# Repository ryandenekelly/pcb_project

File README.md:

# STM32 PCB Project
**Very much a work in progress**

PCB prototype project using KiCad and based on ST32F411RET7. 
The goal is to utilise the SSD1306 or ST7735 LCD displays and RFM69 radio to make a sensor sever / controller.

## Schematic
### MCU

Circuitry to power microcontroller and its nesessary parts.

### Power

USB-C/Battery power and regulator.

### UART
USB-B UART input.

### Radio and Display
Headers for RFM69 radio and LCD displays

### Input
Push button and encoder input with filtering.

## PCB

First version of PCB

### Top Layer

Top layer containing the signals and power.

### Bottom Layer

Bottom layer containing mostly the GND plane, with some signals from vias.

### Future Improvement

Currently in the proccess of assembling pcb. The wrong size capacitors were ordered for C13 and C14, but were assembled with some reworking.
May need re-design on crystal oscilator to use a part that is more easily hand soldered. Boot and reset nets may need reworking.

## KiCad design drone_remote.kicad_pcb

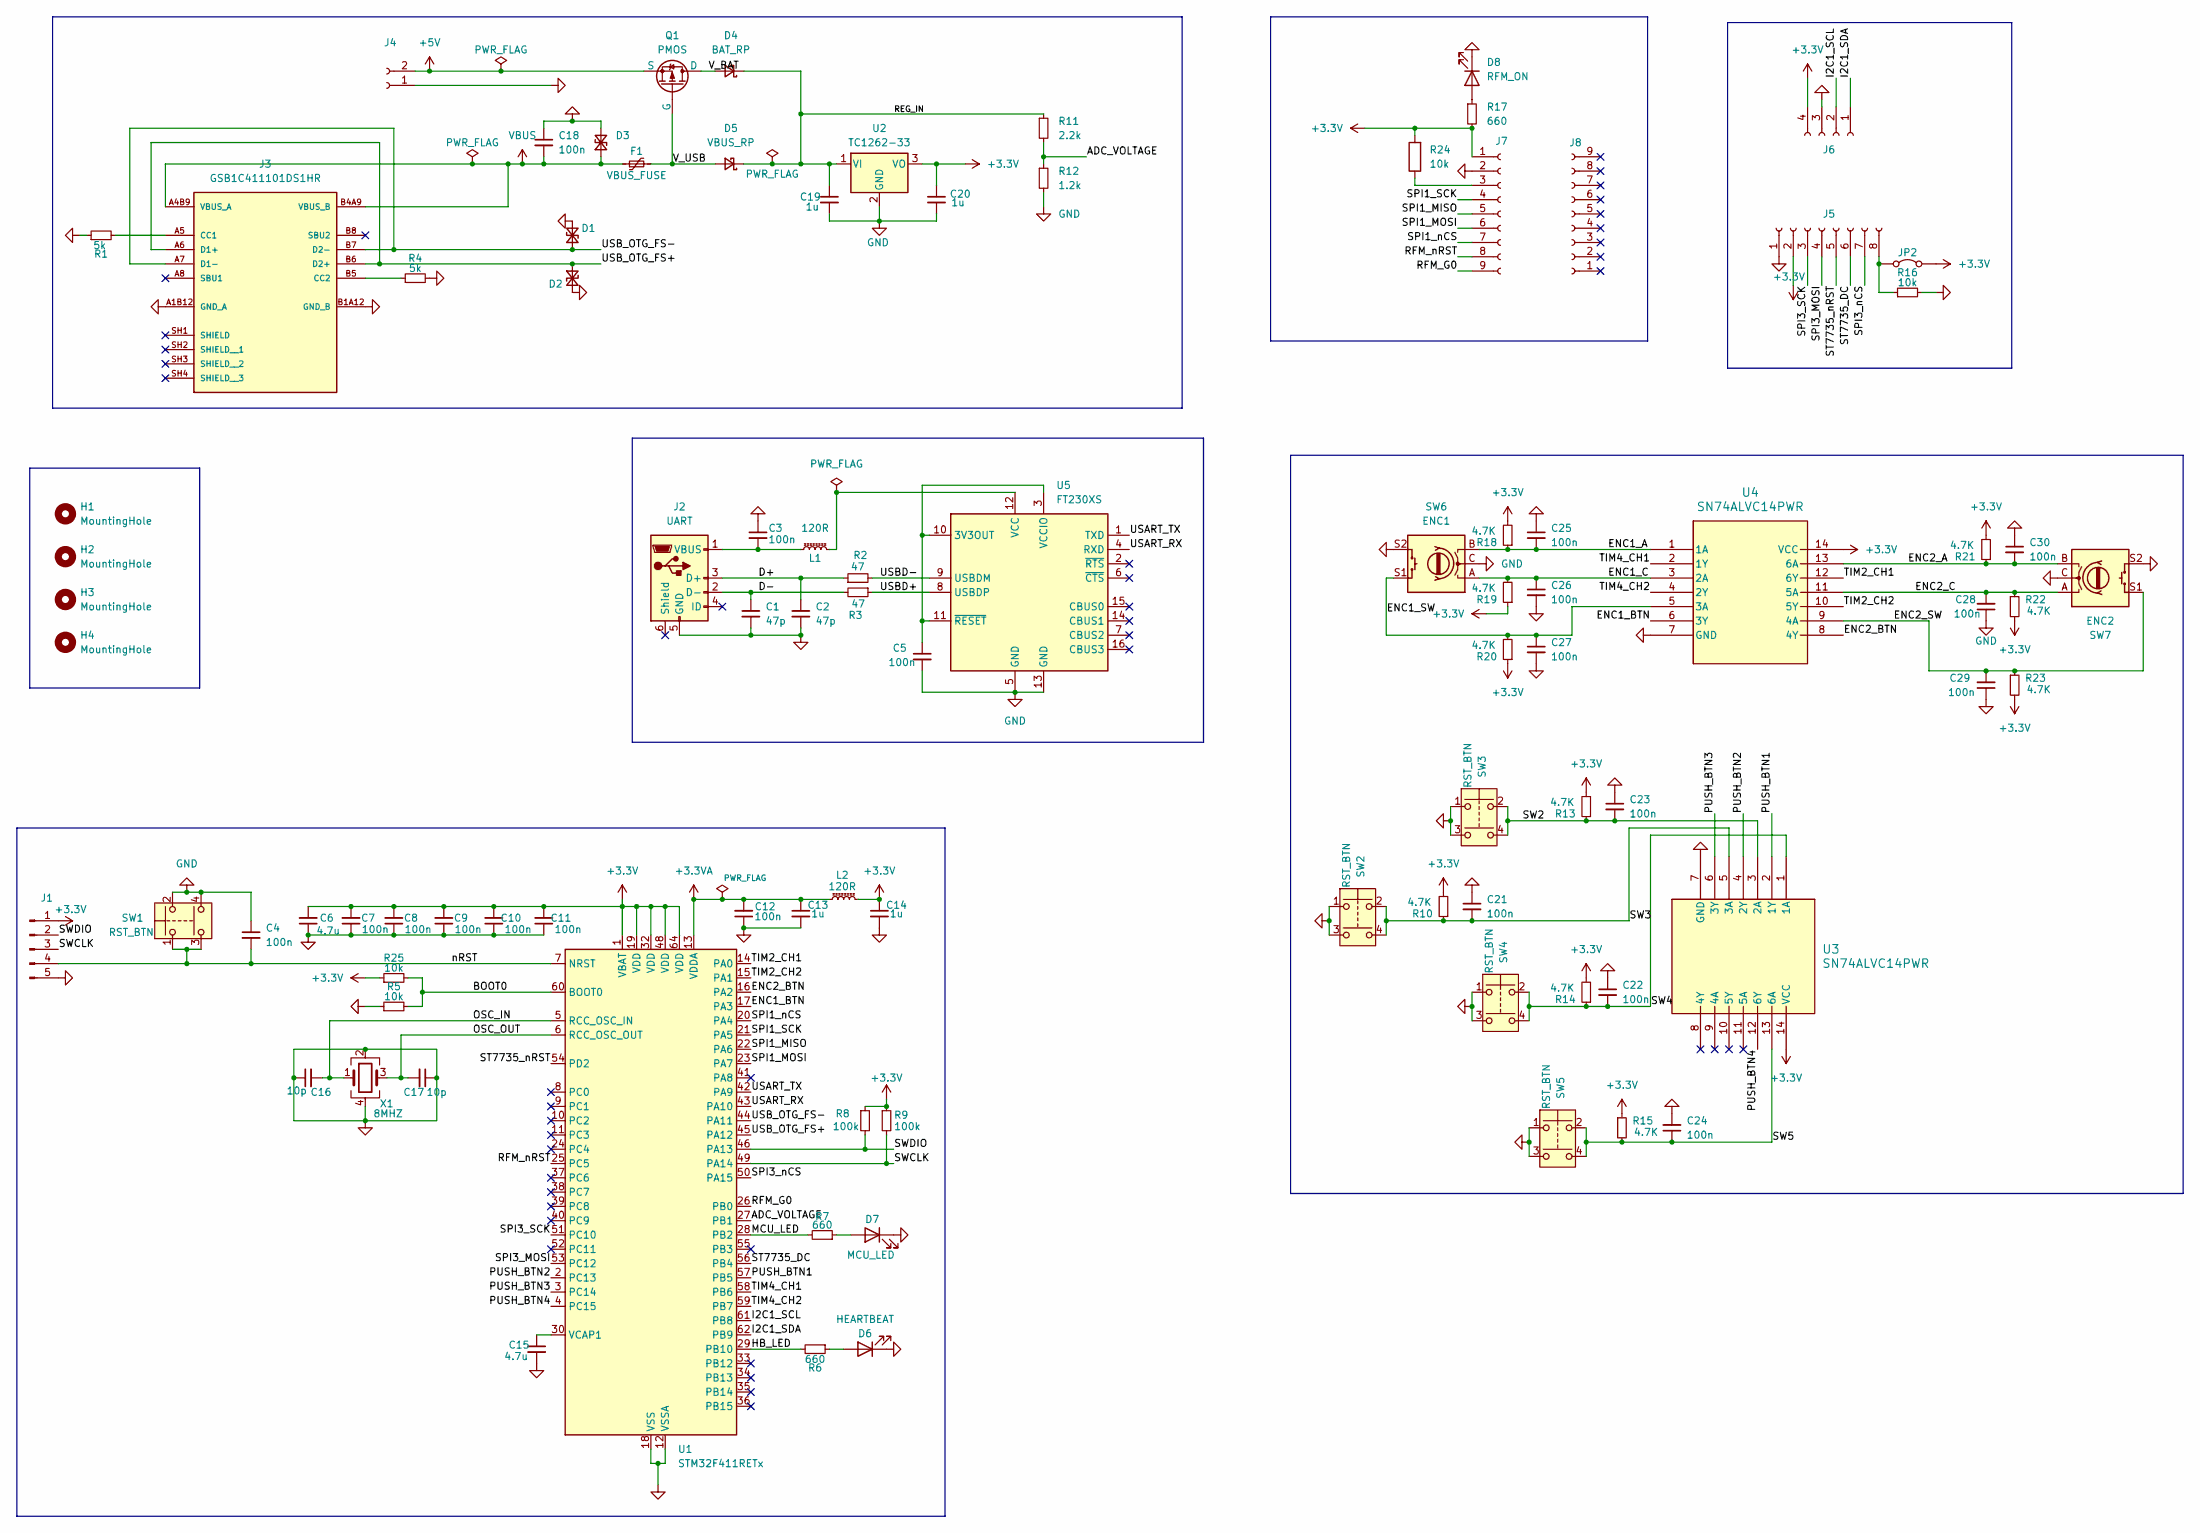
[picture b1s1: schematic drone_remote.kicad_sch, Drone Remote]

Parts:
C1, C2: 47p; C_0402_1005Metric
C3, C4, C5, C18, C21, C22, C23, C24, C25, C26, C27, C28, C29, C30: 100n; C_0805_2012Metric
C6: 4.7u; C_0402_1005Metric
C7, C8, C9, C10, C11, C12: 100n; C_0402_1005Metric
C13, C14: 1u; C_0402_1005Metric
C15: 4.7u; C_0805_2012Metric
C16, C17: 10p; C_0402_1005Metric
C19, C20: 1u; C_0805_2012Metric
D1: DN_TVS; D_SOD-323
D2: DP_TVS; D_SOD-323
D3: D_TVS_Small; D_SOD-323
D4: BAT_RP; D_0805_2012Metric
D5: VBUS_RP; D_0805_2012Metric
D6: HEARTBEAT; LED_0603_1608Metric
D7: MCU_LED; LED_0603_1608Metric
D8: RFM_ON; LED_0603_1608Metric
F1: VBUS_FUSE; Fuse_0805_2012Metric
H1, H2, H3, H4: MountingHole; MountingHole_2.7mm_M2.5
J1: Conn_01x05_Pin; PinHeader_1x05_P2.54mm_Vertical
J2: UART; CONN5_USB1734035_NP_TEC
J3: GSB1C411101DS1HR; AMPHENOL_GSB1C411101DS1HR; PARTREV AX3
J4: Conn_01x02_Socket; PinHeader_1x02_P2.54mm_Vertical
J5: Conn_01x08_Socket; PinSocket_1x08_P2.54mm_Vertical
J6: Conn_01x04_Socket; PinSocket_1x04_P2.54mm_Vertical
J7, J8: Conn_01x09_Socket; PinSocket_1x09_P2.54mm_Vertical
JP2: Jumper_2_Bridged; PinHeader_1x02_P2.54mm_Vertical
L1, L2: 120R; L_0603_1608Metric
Q1: PMOS; TSOT-23_HandSoldering
R1, R4: 5k; R_0805_2012Metric
R2, R3: 47; R_0805_2012Metric
R5, R16, R25: 10k; R_0805_2012Metric
R6, R7, R17: 660; R_0805_2012Metric
R8, R9: 100k; R_0805_2012Metric
R10, R13, R14, R15, R18, R19, R20, R21, R22, R23: 4.7K; R_0805_2012Metric
R11: 2.2k; R_0805_2012Metric
R12: 1.2k; R_0805_2012Metric
R24: 10k; R_0402_1005Metric
SW1, SW2, SW3, SW4, SW5: RST_BTN; SW_1825910-6-4
SW6: ENC1; RotaryEncoder_Alps_EC11E-Switch_Vertical_H20mm
SW7: ENC2; RotaryEncoder_Alps_EC11E-Switch_Vertical_H20mm
U1: STM32F411RETx; LQFP-64_10x10mm_P0.5mm
U2: TC1262-33; SOT-223-3_TabPin2
U3, U4: SN74ALVC14PWR; PW14
U5: FT230XS; SSOP-16_3.9x4.9mm_P0.635mm
X1: 8MHZ; SMD_ECS-80-10-3M-TR_ECS

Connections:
+3.3V: C6.2, C7.2, C8.2, C9.2, C10.2, C11.2, C14.1, C20.1, J1.1, J5.2, J6.4, J7.1, JP2.2 (B), L2.2, R8.1, R9.1, R10.2, R13.2, R14.2, R15.1, R17.2, R18.2, R19.1, R20.1, R21.2, R22.2, R23.2, R24.2, R25.1, U1.1 (VBAT), U1.19 (VDD), U1.32 (VDD), U1.48 (VDD), U1.64 (VDD), U2.3 (VO), U3.14 (VCC), U4.14 (VCC)
+3.3VA: C12.2, C13.1, L2.1, U1.13 (VDDA)
+5V: J4.2, Q1.3 (S)
/ADC_VOLTAGE: R11.2, R12.1, U1.27 (PB1)
/BOOT0: R5.2, R25.2, U1.60 (BOOT0)
/D+: C2.1, J2.3 (D+), R2.1
/D-: C1.1, J2.2 (D-), R3.2
/ENC1_A: C25.2, R18.1, SW6.B, U4.1 (1A)
/ENC1_BTN: U1.17 (PA3), U4.6 (3Y)
/ENC1_C: C26.1, R19.2, SW6.A, U4.3 (2A)
/ENC1_SW: C27.1, R20.2, SW6.S1, U4.5 (3A)
/ENC2_A: C30.2, R21.1, SW7.B, U4.13 (6A)
/ENC2_BTN: U1.16 (PA2), U4.8 (4Y)
/ENC2_C: C28.2, R22.1, SW7.A, U4.11 (5A)
/ENC2_SW: C29.2, R23.1, SW7.S1, U4.9 (4A)
/HB_LED: R6.2, U1.29 (PB10)
/I2C1_SCL: J6.2, U1.61 (PB8)
/I2C1_SDA: J6.1, U1.62 (PB9)
/MCU_LED: R7.2, U1.28 (PB2)
/OSC_IN: C16.2, U1.5 (RCC_OSC_IN), X1.1
/OSC_OUT: C17.2, U1.6 (RCC_OSC_OUT), X1.3
/PUSH_BTN1: U1.57 (PB5), U3.2 (1Y)
/PUSH_BTN2: U1.2 (PC13), U3.4 (2Y)
/PUSH_BTN3: U1.3 (PC14), U3.6 (3Y)
/PUSH_BTN4: U1.4 (PC15), U3.12 (6Y)
/REG_IN: C19.1, D4.1 (K), D5.1 (K), R11.1, U2.1 (VI)
/RFM_G0: J7.9, U1.26 (PB0)
/RFM_nRST: J7.8, U1.25 (PC5)
/SPI1_MISO: J7.5, U1.22 (PA6)
/SPI1_MOSI: J7.6, U1.23 (PA7)
/SPI1_SCK: J7.4, U1.21 (PA5)
/SPI1_nCS: J7.7, U1.20 (PA4)
/SPI3_MOSI: J5.4, U1.53 (PC12)
/SPI3_SCK: J5.3, U1.51 (PC10)
/SPI3_nCS: J5.7, U1.50 (PA15)
/ST7735_DC: J5.6, U1.56 (PB4)
/ST7735_nRST: J5.5, U1.54 (PD2)
/SW2: C23.2, R13.1, SW3.2, SW3.4, U3.3 (2A)
/SW3: C21.2, R10.1, SW2.2, SW2.4, U3.5 (3A)
/SW4: C22.2, R14.1, SW4.2, SW4.4, U3.1 (1A)
/SW5: C24.1, R15.2, SW5.2, SW5.4, U3.13 (6A)
/SWCLK: J1.3, R9.2, U1.49 (PA14)
/SWDIO: J1.2, R8.2, U1.46 (PA13)
/TIM2_CH1: U1.14 (PA0), U4.12 (6Y)
/TIM2_CH2: U1.15 (PA1), U4.10 (5Y)
/TIM4_CH1: U1.58 (PB6), U4.2 (1Y)
/TIM4_CH2: U1.59 (PB7), U4.4 (2Y)
/USART_RX: U1.43 (PA10), U5.4 (RXD)
/USART_TX: U1.42 (PA9), U5.1 (TXD)
/USBD+: R3.1, U5.8 (USBDP)
/USBD-: R2.2, U5.9 (USBDM)
/USB_OTG_FS+: D2.1 (A1), J3.A6 (D1+), J3.B6 (D2+), U1.45 (PA12)
/USB_OTG_FS-: D1.1 (A1), J3.A7 (D1-), J3.B7 (D2-), U1.44 (PA11)
/V_BAT: D4.2 (A), Q1.1 (D)
/V_USB: D5.2 (A), F1.2, Q1.2 (G)
/nRST: C4.2, J1.4, SW1.1, SW1.3, U1.7 (NRST)
GND: C1.2, C2.2, C3.1, C4.1, C5.2, C6.1, C7.1, C8.1, C9.1, C10.1, C11.1, C12.1, C13.2, C14.2, C15.2, C16.1, C17.1, C18.1, C19.2, C20.2, C21.1, C22.1, C23.1, C24.2, C25.1, C26.2, C27.2, C28.1, C29.1, C30.1, D1.2 (A2), D2.2 (A2), D3.2 (A2), D6.1 (K), D7.1 (K), D8.1 (K), J1.5, J2.5 (GND), J3.A1B12 (GND_A), J3.B1A12 (GND_B), J4.1, J5.1, J6.3, J7.2, R1.1, R4.2, R5.1, R12.2, R16.2, SW1.2, SW1.4, SW2.1, SW2.3, SW3.1, SW3.3, SW4.1, SW4.3, SW5.1, SW5.3, SW6.C, SW6.S2, SW7.C, SW7.S2, U1.12 (VSSA), U1.18 (VSS), U1.31 (VSS), U1.47 (VSS), U1.63 (VSS), U2.2 (GND), U3.7 (GND), U4.7 (GND), U5.5 (GND), U5.13 (GND), X1.2, X1.4
unnamed: D6.2 (A), R6.1
unnamed: D7.2 (A), R7.1
unnamed: D8.2 (A), R17.1
unnamed: C3.2, J2.1 (VBUS), L1.1
unnamed: J3.A5 (CC1), R1.2
unnamed: J3.B5 (CC2), R4.1
unnamed: J5.8, JP2.1 (A), R16.1
unnamed: J7.3, R24.1
unnamed: C15.1, U1.30 (VCAP1)
unnamed: C5.1, U5.3 (VCCIO), U5.10 (3V3OUT), U5.11 (~RESET)
unnamed: L1.2, U5.12 (VCC)
VBUS: C18.2, D3.1 (A1), F1.1, J3.A4B9 (VBUS_A), J3.B4A9 (VBUS_B)

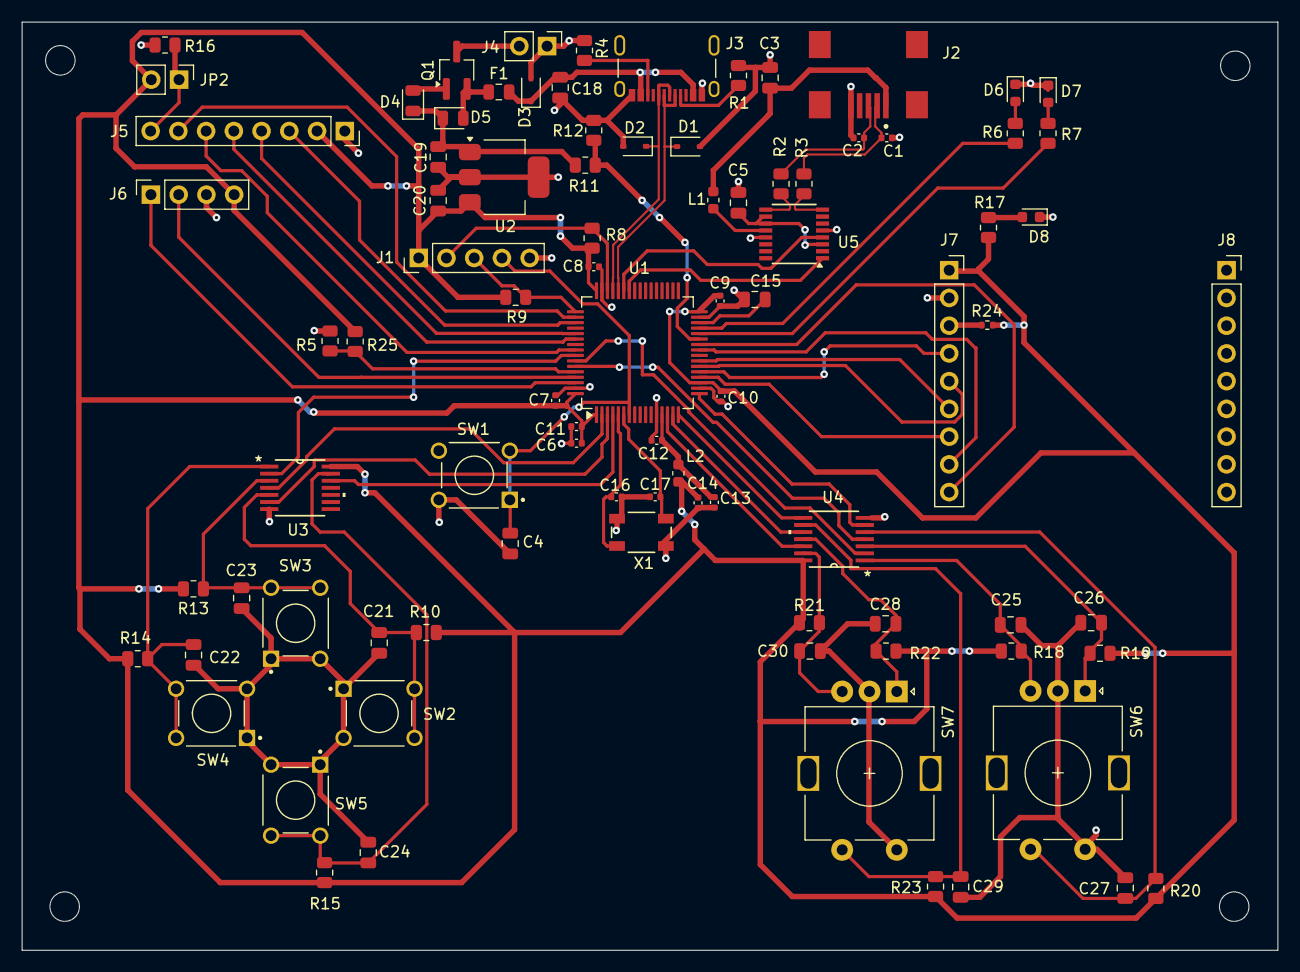
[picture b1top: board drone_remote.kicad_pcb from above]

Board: 2 copper layers, 115.0 x 85.0 mm, 93 parts (0 on the bottom side), 69 nets.

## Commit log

2025-01-16 finalised first version of pcb, generated manufacturing files, cleaned up file dir
2025-01-16 updated license
2025-01-16 some images
2025-01-16 more images
2025-02-07 Update README.md about assembly progress
